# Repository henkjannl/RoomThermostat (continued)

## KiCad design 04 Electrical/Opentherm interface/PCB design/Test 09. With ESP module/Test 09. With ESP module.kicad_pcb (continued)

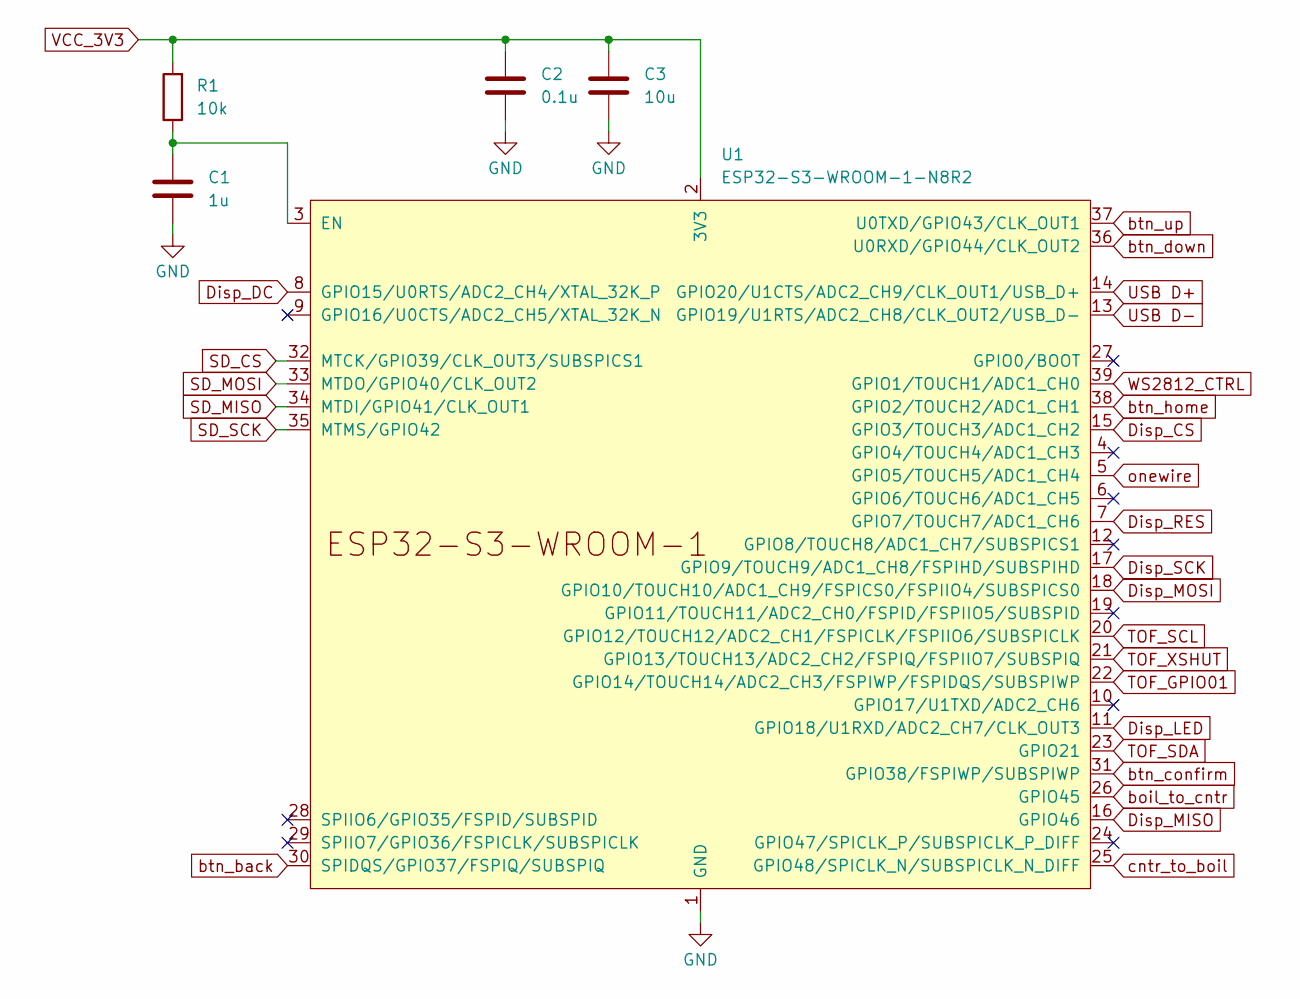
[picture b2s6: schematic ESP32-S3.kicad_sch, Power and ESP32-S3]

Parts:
C1: 1u; C_0603_1608Metric; LCSC Part # C15849
C2: 0.1u; C_0603_1608Metric; LCSC Part # C14663
C3: 10u; C_0402_1005Metric; LCSC Part # C15525
R1: 10k; R_0201_0603Metric; LCSC Part # C25804
U1: ESP32-S3-WROOM-1-N8R2; ESP32-S3-WROOM-1; LCSC Part # C2913204

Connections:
Disp_CS: U1.15 (GPIO3/TOUCH3/ADC1_CH2); also elsewhere on the board
Disp_DC: U1.8 (GPIO15/U0RTS/ADC2_CH4/XTAL_32K_P); also elsewhere on the board
Disp_LED: U1.11 (GPIO18/U1RXD/ADC2_CH7/CLK_OUT3); also elsewhere on the board
Disp_MISO: U1.16 (GPIO46); also elsewhere on the board
Disp_MOSI: U1.18 (GPIO10/TOUCH10/ADC1_CH9/FSPICS0/FSPIIO4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); also elsewhere on the board
Disp_RES: U1.7 (GPIO7/TOUCH7/ADC1_CH6); also elsewhere on the board
Disp_SCK: U1.17 (GPIO9/TOUCH9/ADC1_CH8/FSPIHD/SUBSPIHD); also elsewhere on the board
GND: C1.2, C2.2, C3.2, U1.1 (GND), U1.40 (GND), U1.41 (GND); also elsewhere on the board
unnamed: C1.1, R1.1, U1.3 (EN)
SD_CS: U1.32 (MTCK/GPIO39/CLK_OUT3/SUBSPICS1); also elsewhere on the board
SD_MISO: U1.34 (MTDI/GPIO41/CLK_OUT1); also elsewhere on the board
SD_MOSI: U1.33 (MTDO/GPIO40/CLK_OUT2); also elsewhere on the board
SD_SCK: U1.35 (MTMS/GPIO42); also elsewhere on the board
TOF_GPIO01: U1.22 (GPIO14/TOUCH14/ADC2_CH3/FSPIWP/FSPIDQS/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); also elsewhere on the board
TOF_SCL: U1.20 (GPIO12/TOUCH12/ADC2_CH1/FSPICLK/FSPIIO6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); also elsewhere on the board
TOF_SDA: U1.23 (GPIO21); also elsewhere on the board
TOF_XSHUT: U1.21 (GPIO13/TOUCH13/ADC2_CH2/FSPIQ/FSPIIO7/S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); also elsewhere on the board
USB D+: U1.14 (GPIO20/U1CTS/ADC2_CH9/CLK_OUT1/USB_D+); also elsewhere on the board
USB D-: U1.13 (GPIO19/U1RTS/ADC2_CH8/CLK_OUT2/USB_D-); also elsewhere on the board
VCC_3V3: C2.1, C3.1, R1.2, U1.2 (3V3); also elsewhere on the board
WS2812_CTRL: U1.39 (GPIO1/TOUCH1/ADC1_CH0); also elsewhere on the board
boil_to_cntr: U1.26 (GPIO45); also elsewhere on the board
btn_back: U1.30 (SPIDQS/GPIO37/FSPIQ/SUBSPIQ); also elsewhere on the board
btn_confirm: U1.31 (GPIO38/FSPIWP/SUBSPIWP); also elsewhere on the board
btn_down: U1.36 (U0RXD/GPIO44/CLK_OUT2); also elsewhere on the board
btn_home: U1.38 (GPIO2/TOUCH2/ADC1_CH1); also elsewhere on the board
btn_up: U1.37 (U0TXD/GPIO43/CLK_OUT1); also elsewhere on the board
cntr_to_boil: U1.25 (GPIO48/SPICLK_N/SUBSPICLK_N_DIFF); also elsewhere on the board
onewire: U1.5 (GPIO5/TOUCH5/ADC1_CH4); also elsewhere on the board

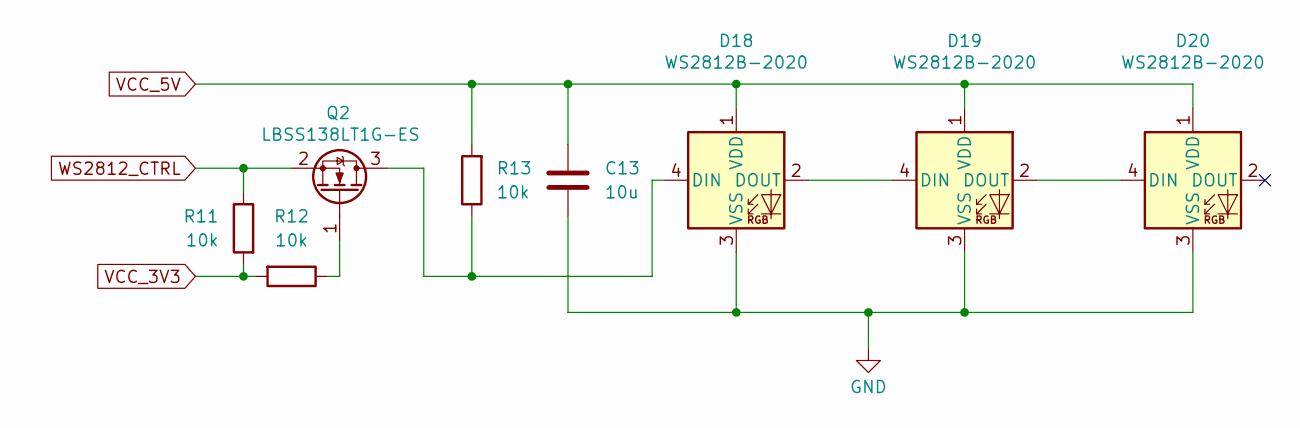
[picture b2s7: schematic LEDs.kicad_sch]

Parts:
C13: 10u; C_0402_1005Metric; LCSC Part # C15525
D18, D19, D20: WS2812B-2020; LED_WS2812B_PLCC4_5.0x5.0mm_P3.2mm; LCSC Part # C965555
Q2: LBSS138LT1G-ES; SOT-23; LCSC Part # C5224262
R11, R12, R13: 10k; R_0201_0603Metric; LCSC Part # C25804

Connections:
GND: C13.2, D18.3 (VSS), D19.3 (VSS), D20.3 (VSS); also elsewhere on the board
unnamed: D18.4 (DIN), Q2.3 (D), R13.1
unnamed: D18.2 (DOUT), D19.4 (DIN)
unnamed: D19.2 (DOUT), D20.4 (DIN)
unnamed: Q2.1 (G), R12.1
VCC_3V3: R11.2, R12.2; also elsewhere on the board
VCC_5V: C13.1, D18.1 (VDD), D19.1 (VDD), D20.1 (VDD), R13.2; also elsewhere on the board
WS2812_CTRL: Q2.2 (S), R11.1; also elsewhere on the board

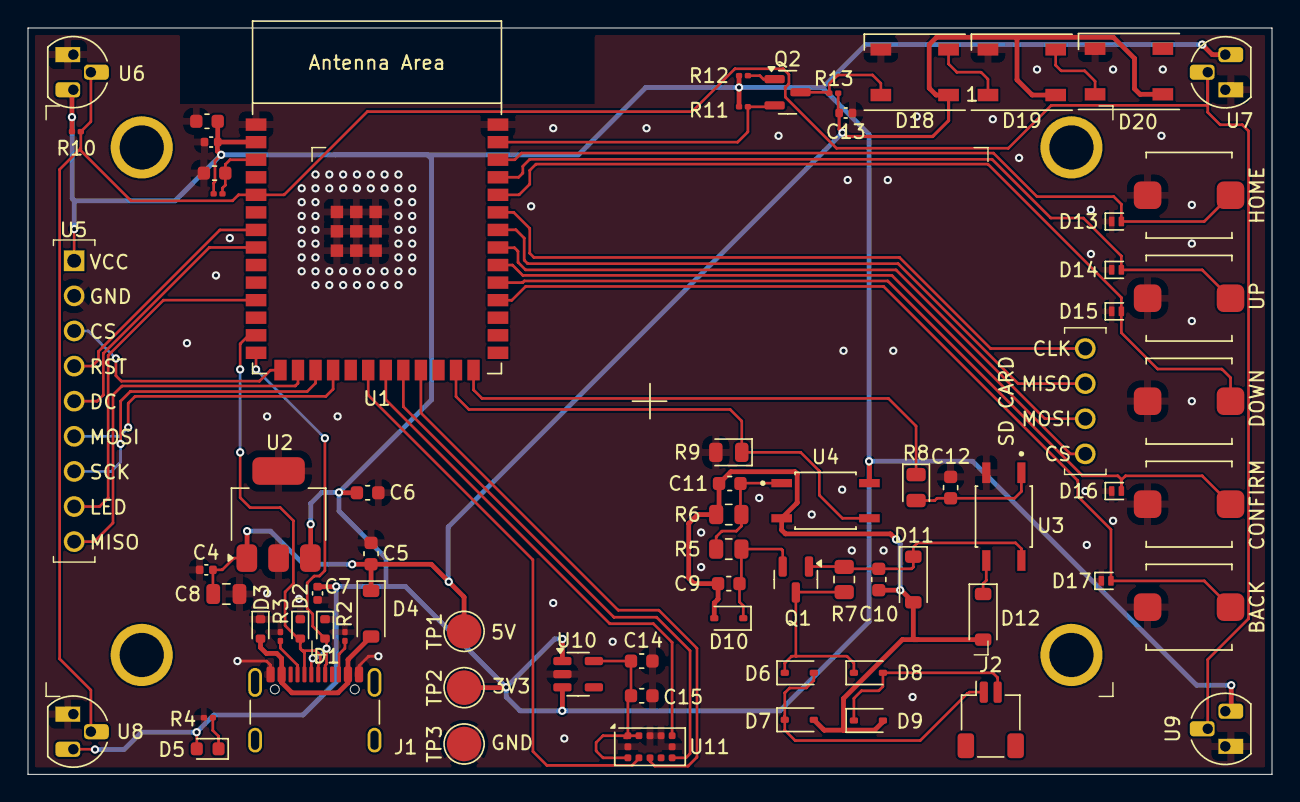
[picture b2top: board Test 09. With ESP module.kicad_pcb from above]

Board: 2 copper layers, 90.0 x 54.0 mm, 71 parts (0 on the bottom side), 48 nets.

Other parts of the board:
D13, D14, D15, D16, D17: LESD8D3.3CAT5G-ES; D_SOD-882
SW1: btn_home; SW_Push_SPEH
SW2: btn_up; SW_Push_SPEH
SW3: btn_down; SW_Push_SPEH
SW4: btn_confirm; SW_Push_SPEH
SW5: btn_back; SW_Push_SPEH

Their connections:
GND: D13.1 (A1), D14.1 (A1), D15.1 (A1), D16.1 (A1), D17.1 (A1), SW1.1, SW2.1, SW3.1, SW4.1, SW5.1; also elsewhere on the board
btn_back: D17.2 (A2), SW5.2; also elsewhere on the board
btn_confirm: D16.2 (A2), SW4.2; also elsewhere on the board
btn_down: D15.2 (A2), SW3.2; also elsewhere on the board
btn_home: D13.2 (A2), SW1.2; also elsewhere on the board
btn_up: D14.2 (A2), SW2.2; also elsewhere on the board

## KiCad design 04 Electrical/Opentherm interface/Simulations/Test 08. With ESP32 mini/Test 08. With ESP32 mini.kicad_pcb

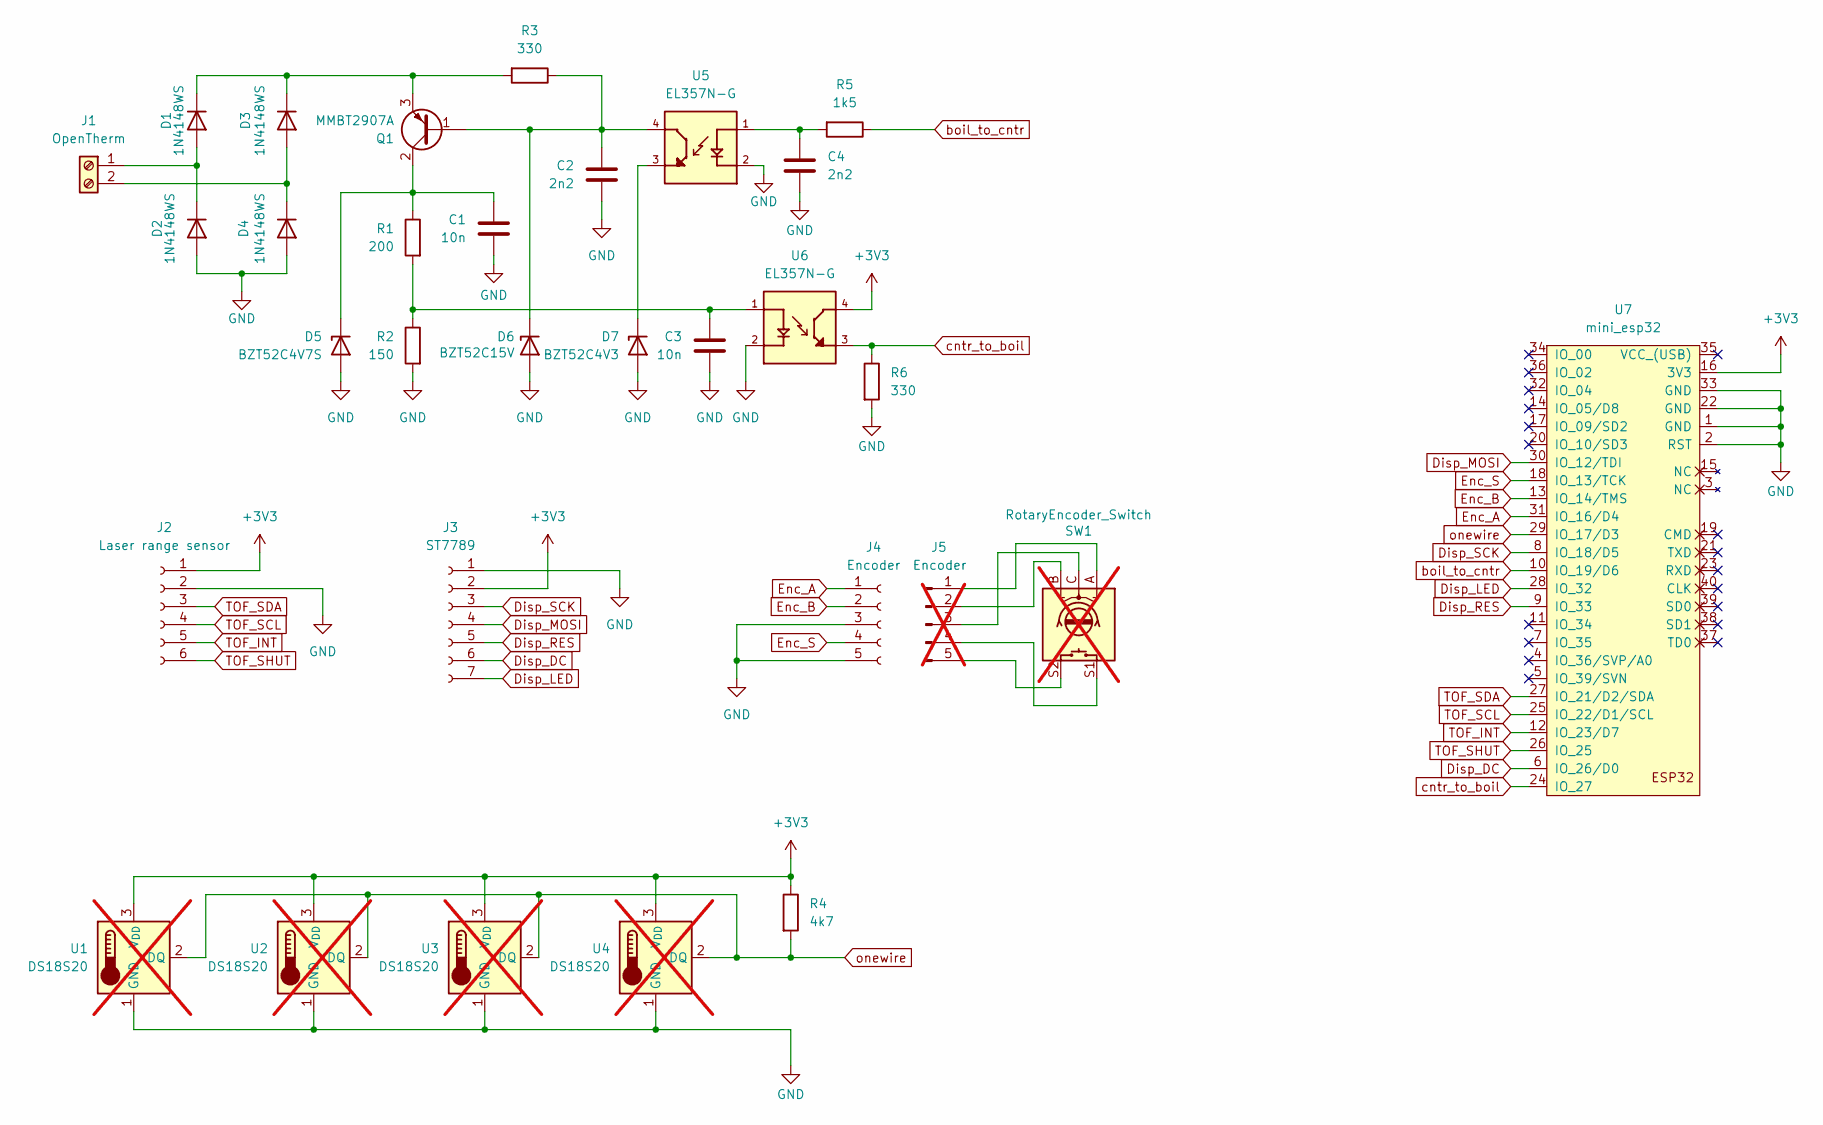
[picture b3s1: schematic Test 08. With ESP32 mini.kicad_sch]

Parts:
C1, C3: 10n; C_0603_1608Metric
C2, C4: 2n2; C_0603_1608Metric
D1, D2, D3, D4: 1N4148WS; D_SOD-323
D5: BZT52C4V7S; D_SOD-323
D6: BZT52C15V; D_SOD-123
D7: BZT52C4V3; D_SOD-123
J1: OpenTherm; TerminalBlock_bornier-2_P5.08mm
J2: Laser range sensor; PinHeader_1x06_P2.54mm_Vertical
J3: ST7789; PinHeader_1x07_P2.54mm_Vertical
J4: Encoder; PinHeader_1x05_P2.54mm_Vertical
J5: Encoder; not fitted
Q1: MMBT2907A; SOT-23
R1: 200; R_0805_2012Metric
R2: 150; R_0805_2012Metric
R3: 330; R_0805_2012Metric
R4: 4k7; R_0805_2012Metric
R5: 1k5; D_0805_2012Metric
R6: 330; D_0805_2012Metric
SW1: RotaryEncoder_Switch; not fitted
U1, U2, U3, U4: DS18S20; TO-92L_HandSolder; not fitted
U5, U6: EL357N-G; OPTO_EL357N-G; PARTREV 6
U7: mini_esp32; ESP32_mini

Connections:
+3V3: J2.1, J3.2, R4.1, U1.3 (V_{DD}), U2.3 (V_{DD}), U3.3 (V_{DD}), U4.3 (V_{DD}), U6.4, U7.16 (3V3)
Disp_DC: J3.6, U7.6 (IO_26/D0)
Disp_LED: J3.7, U7.28 (IO_32)
Disp_MOSI: J3.4, U7.30 (IO_12/TDI)
Disp_RES: J3.5, U7.9 (IO_33)
Disp_SCK: J3.3, U7.8 (IO_18/D5)
Enc_A: J4.1, U7.31 (IO_16/D4)
Enc_B: J4.2, U7.13 (IO_14/TMS)
Enc_S: J4.4, U7.18 (IO_13/TCK)
GND: C1.1, C2.2, C3.1, C4.1, D2.2 (A), D4.2 (A), D5.2 (A), D6.2 (A), D7.2 (A), J2.2, J3.1, J4.3, J4.5, R2.2, R6.2, U1.1 (GND), U2.1 (GND), U3.1 (GND), U4.1 (GND), U5.2, U6.2, U7.1 (GND), U7.2 (RST), U7.22 (GND), U7.33 (GND)
unnamed: C3.2, R1.2, R2.1, U6.1
unnamed: C4.2, R5.2, U5.1
unnamed: D1.2 (A), D2.1 (K), J1.1
unnamed: D1.1 (K), D3.1 (K), Q1.3 (E), R3.2
unnamed: D3.2 (A), D4.1 (K), J1.2
unnamed: C1.2, D5.1 (K), Q1.2 (C), R1.1
unnamed: C2.1, D6.1 (K), Q1.1 (B), R3.1, U5.4
unnamed: D7.1 (K), U5.3
unnamed: J5.1, SW1.A
unnamed: J5.2, SW1.B
unnamed: J5.3, SW1.C
unnamed: J5.4, SW1.S1
unnamed: J5.5, SW1.S2
TOF_INT: J2.5, U7.12 (IO_23/D7)
TOF_SCL: J2.4, U7.25 (IO_22/D1/SCL)
TOF_SDA: J2.3, U7.27 (IO_21/D2/SDA)
TOF_SHUT: J2.6, U7.26 (IO_25)
boil_to_cntr: R5.1, U7.10 (IO_19/D6)
cntr_to_boil: R6.1, U6.3, U7.24 (IO_27)
onewire: R4.2, U1.2 (DQ), U2.2 (DQ), U3.2 (DQ), U4.2 (DQ), U7.29 (IO_17/D3)

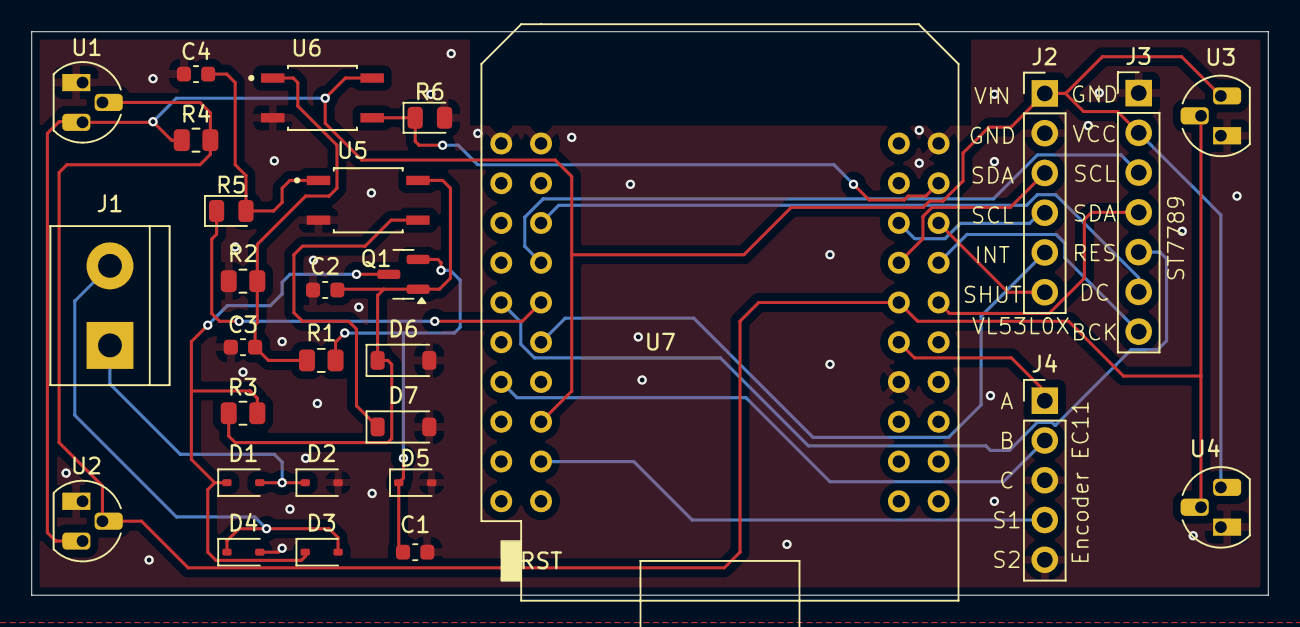
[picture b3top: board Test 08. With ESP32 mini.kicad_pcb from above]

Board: 2 copper layers, 79.0 x 36.0 mm, 29 parts (0 on the bottom side), 25 nets.

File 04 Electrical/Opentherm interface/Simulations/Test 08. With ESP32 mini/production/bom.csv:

Designator,Footprint,Quantity,Value,LCSC Part #
"C1, C3",0603,2,10n,
"C2, C4",0603,2,2n2,
"D1, D2, D3, D4",D_SOD-323,4,1N4148WS,
D5,D_SOD-323,1,BZT52C4V7S,
D6,D_SOD-123,1,BZT52C15V,
D7,D_SOD-123,1,BZT52C4V3,
Q1,SOT-23,1,MMBT2907A,
R1,0805,1,200,
R2,0805,1,150,
"R3, R6",0805,2,330,
R4,0805,1,4k7,
R5,0805,1,1k5,
"U5, U6",OPTO_EL357N-G,2,EL357N-G,

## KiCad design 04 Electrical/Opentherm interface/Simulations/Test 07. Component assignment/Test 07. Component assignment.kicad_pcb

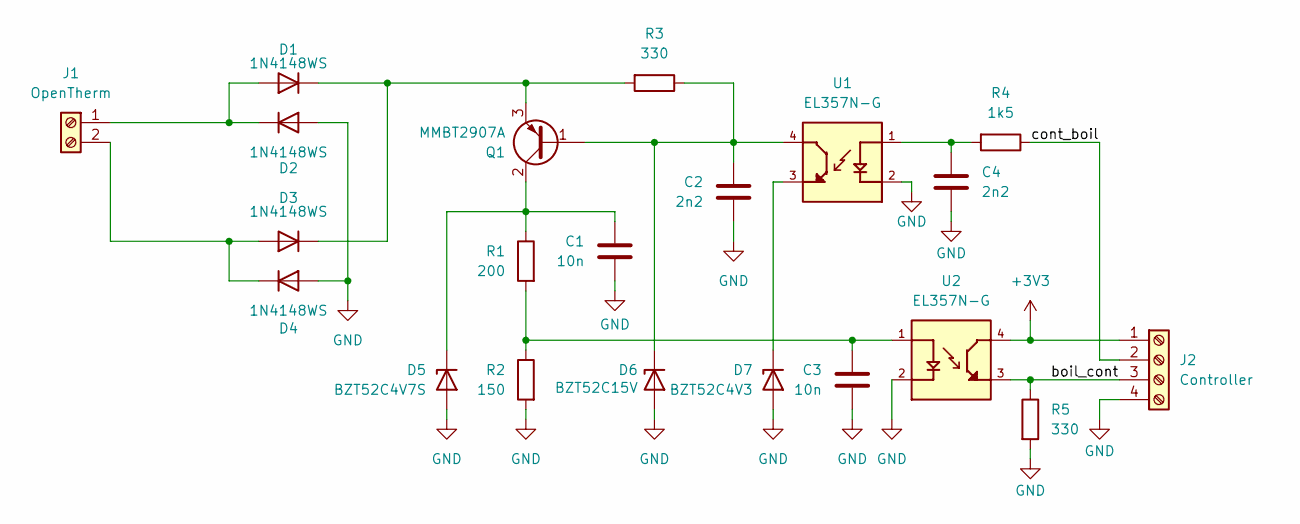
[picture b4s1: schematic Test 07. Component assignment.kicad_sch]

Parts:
C1, C3: 10n; C_0603_1608Metric
C2, C4: 2n2; C_0603_1608Metric
D1, D2, D3, D4: 1N4148WS; D_SOD-323
D5: BZT52C4V7S; D_SOD-323
D6: BZT52C15V; D_SOD-123
D7: BZT52C4V3; D_SOD-123
J1: OpenTherm; TerminalBlock_bornier-2_P5.08mm
J2: Controller; TerminalBlock_bornier-4_P5.08mm
Q1: MMBT2907A; SOT-23
R1: 200; R_0805_2012Metric
R2: 150; R_0805_2012Metric
R3: 330; R_0805_2012Metric
R4: 1k5; R_0805_2012Metric
R5: 330; D_0805_2012Metric
U1, U2: EL357N-G; OPTO_EL357N-G; PARTREV 6

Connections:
+3V3: J2.1, U2.4
/boil_cont: J2.3, R5.1, U2.3
/cont_boil: J2.2, R4.1
GND: C1.1, C2.2, C3.1, C4.1, D2.2 (A), D4.2 (A), D5.2 (A), D6.2 (A), D7.2 (A), J2.4, R2.2, R5.2, U1.2, U2.2
unnamed: C3.2, R1.2, R2.1, U2.1
unnamed: C4.2, R4.2, U1.1
unnamed: D1.2 (A), D2.1 (K), J1.1
unnamed: D1.1 (K), D3.1 (K), Q1.3 (E), R3.2
unnamed: D3.2 (A), D4.1 (K), J1.2
unnamed: C1.2, D5.1 (K), Q1.2 (C), R1.1
unnamed: C2.1, D6.1 (K), Q1.1 (B), R3.1, U1.4
unnamed: D7.1 (K), U1.3

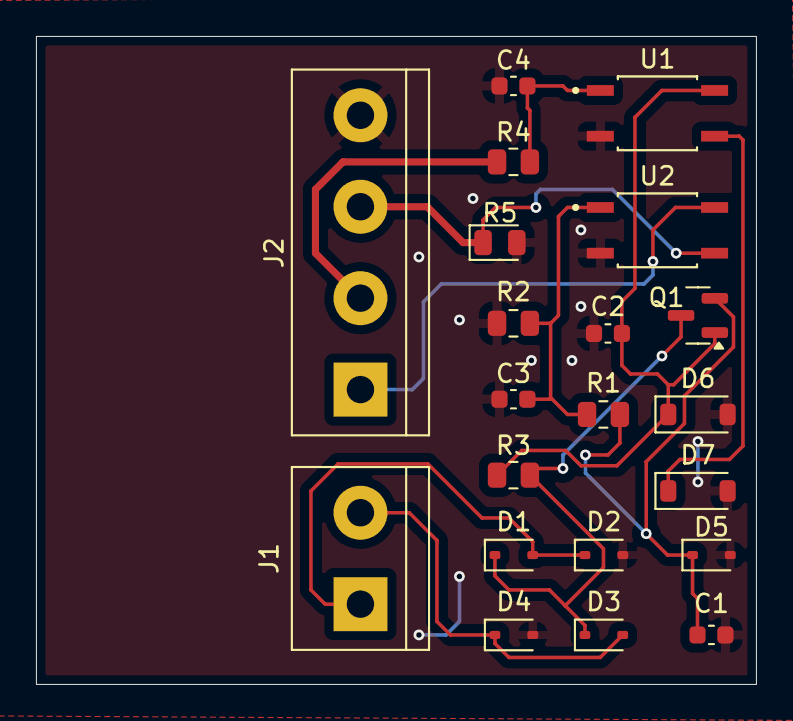
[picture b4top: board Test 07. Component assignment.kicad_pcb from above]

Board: 2 copper layers, 40.0 x 36.0 mm, 21 parts (0 on the bottom side), 12 nets.

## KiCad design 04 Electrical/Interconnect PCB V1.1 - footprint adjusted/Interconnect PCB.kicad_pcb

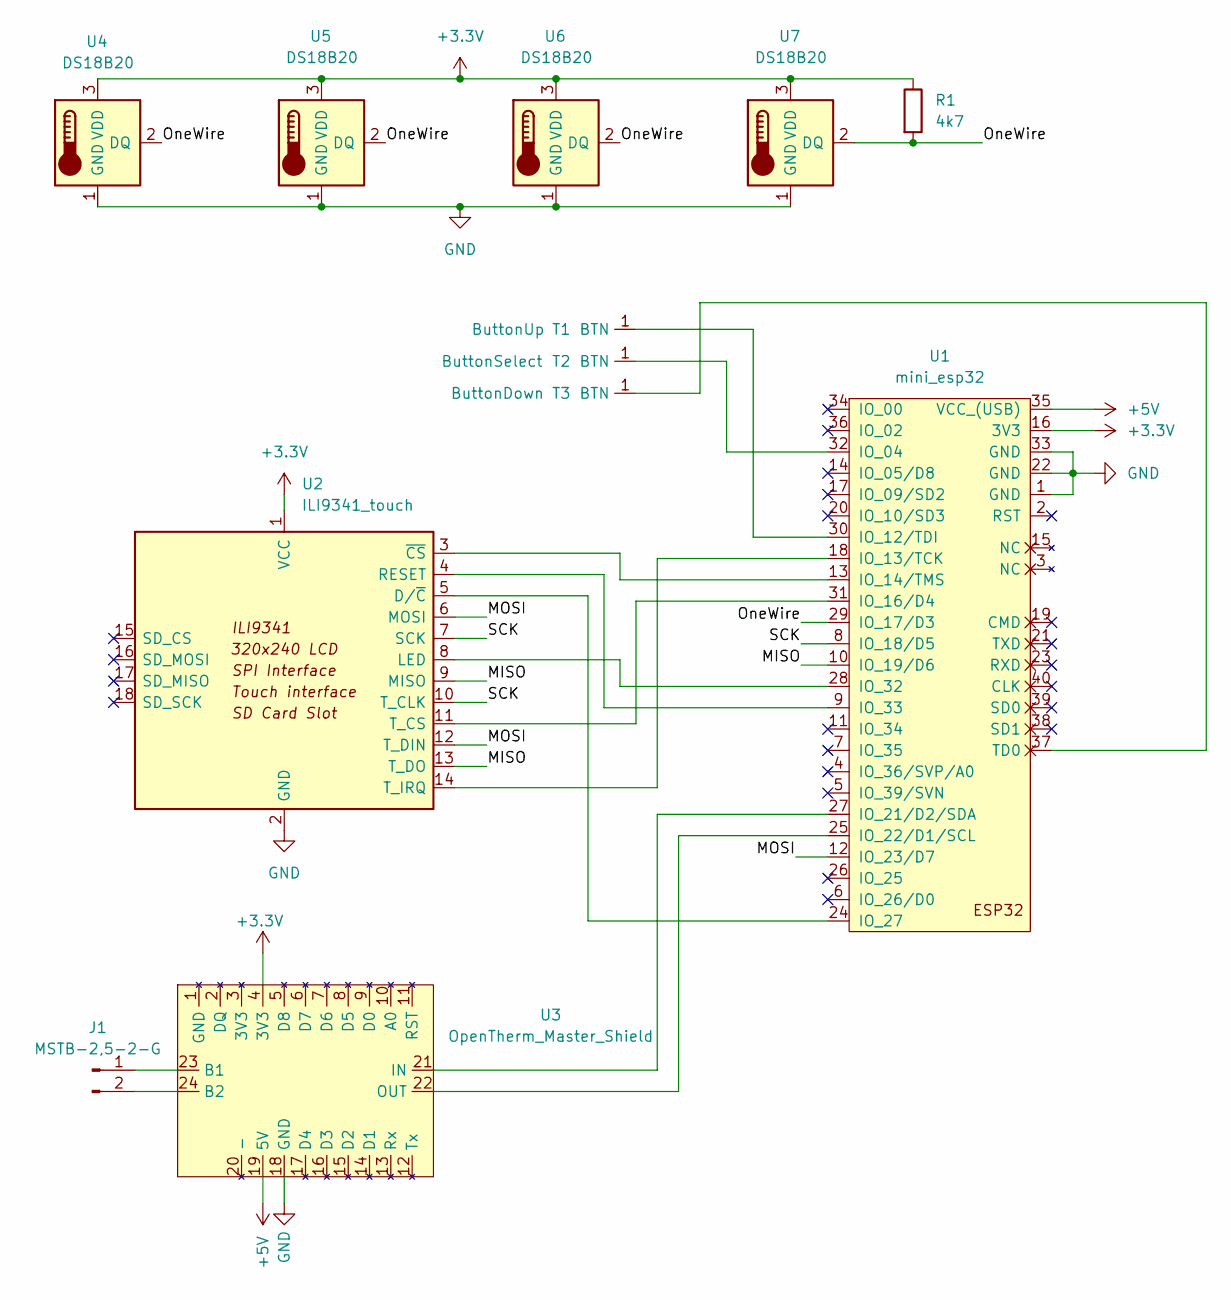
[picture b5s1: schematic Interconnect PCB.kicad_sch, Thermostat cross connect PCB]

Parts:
J1: MSTB-2,5-2-G; Phoenix_MSTB-2,5-2-G
R1: 4k7; Resistor
T1: ButtonUp; TouchPin
T2: ButtonSelect; TouchPin
T3: ButtonDown; TouchPin
U1: mini_esp32; ESP32_mini
U2: ILI9341_touch; ILI9341
U3: OpenTherm_Master_Shield; Opentherm Master Shield
U4, U5, U6, U7: DS18B20

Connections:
+3V3: R1.1, U1.16 (3V3), U2.1 (VCC), U3.4 (3V3), U4.3 (VDD), U5.3 (VDD), U6.3 (VDD), U7.3 (VDD)
+5V: U1.35 (VCC_(USB)), U3.19 (5V)
/MISO: U1.10 (IO_19/D6), U2.9 (MISO), U2.13 (T_DO)
/MOSI: U1.12 (IO_23/D7), U2.6 (MOSI), U2.12 (T_DIN)
/OneWire: R1.2, U1.29 (IO_17/D3), U4.2 (DQ), U5.2 (DQ), U6.2 (DQ), U7.2 (DQ)
/SCK: U1.8 (IO_18/D5), U2.7 (SCK), U2.10 (T_CLK)
GND: U1.1 (GND), U1.22 (GND), U1.33 (GND), U2.2 (GND), U3.18 (GND), U4.1 (GND), U5.1 (GND), U6.1 (GND), U7.1 (GND)
unnamed: J1.1, U3.23 (B1)
unnamed: J1.2, U3.24 (B2)
unnamed: T1.1 (BTN), U1.30 (IO_12/TDI)
unnamed: T2.1 (BTN), U1.32 (IO_04)
unnamed: T3.1 (BTN), U1.37 (TD0)
unnamed: U1.9 (IO_33), U2.4 (RESET)
unnamed: U1.13 (IO_14/TMS), U2.3 (~CS)
unnamed: U1.18 (IO_13/TCK), U2.14 (T_IRQ)
unnamed: U1.24 (IO_27), U2.5 (D/~C)
unnamed: U1.25 (IO_22/D1/SCL), U3.22 (OUT)
unnamed: U1.27 (IO_21/D2/SDA), U3.21 (IN)
unnamed: U1.28 (IO_32), U2.8 (LED)
unnamed: U1.31 (IO_16/D4), U2.11 (T_CS)

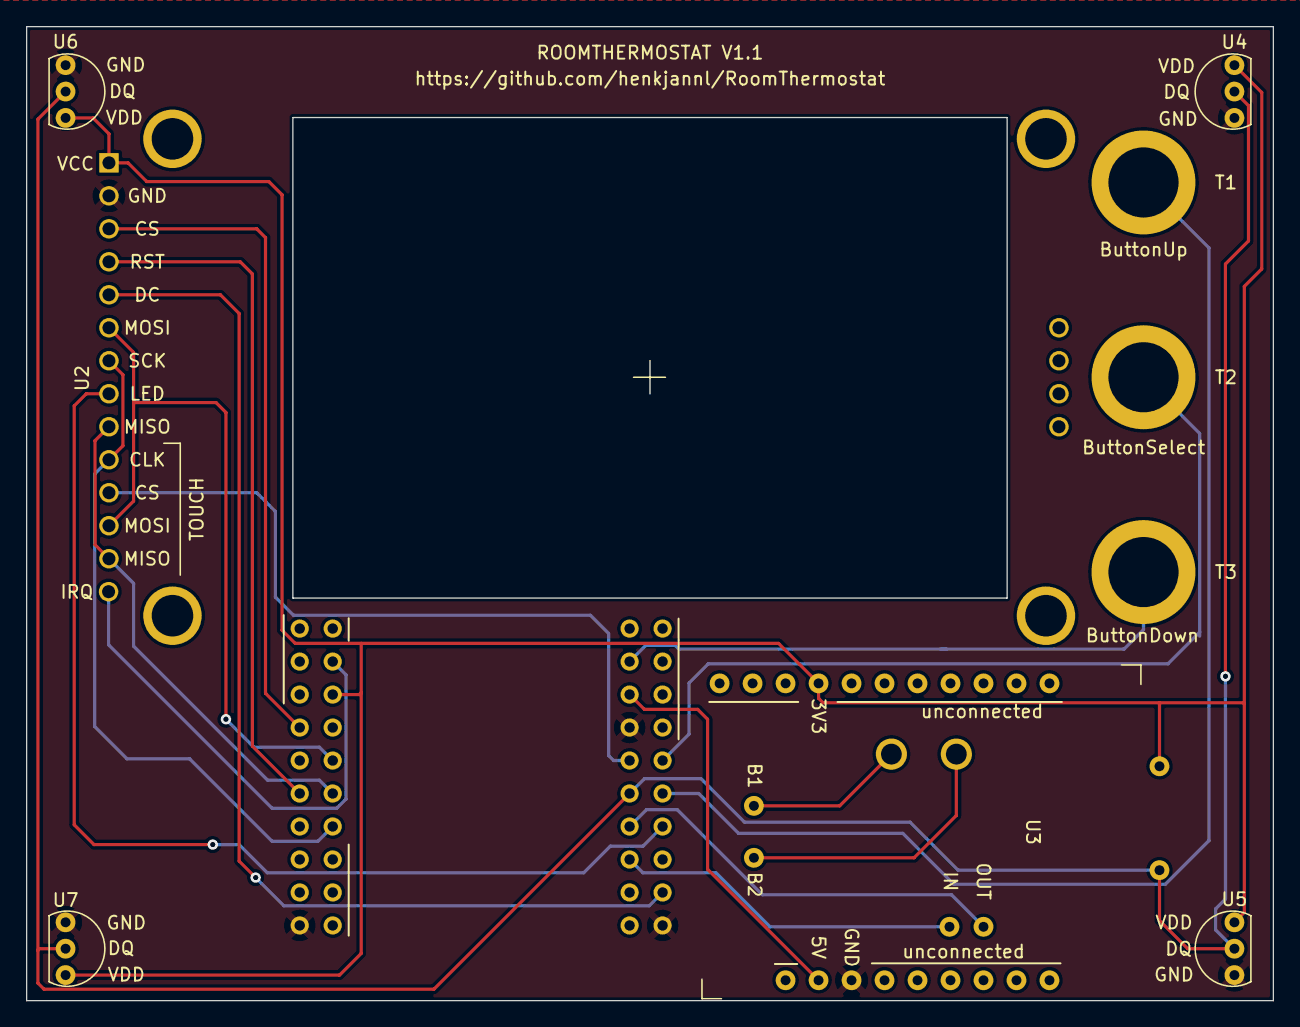
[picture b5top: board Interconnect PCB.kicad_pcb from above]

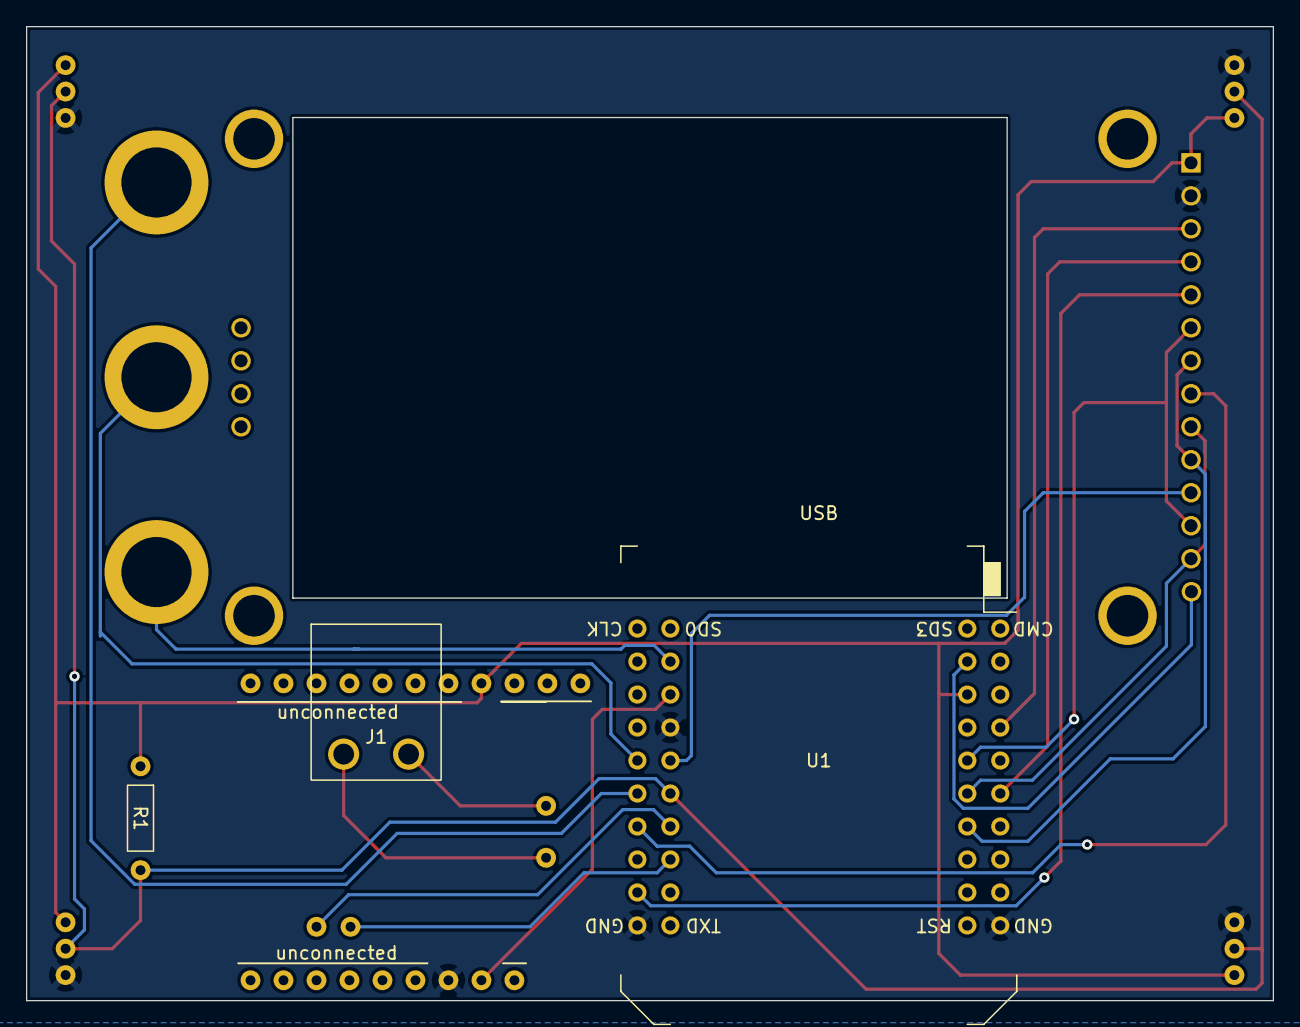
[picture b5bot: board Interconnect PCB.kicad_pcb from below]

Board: 2 copper layers, 96.0 x 75.0 mm, 12 parts (3 on the bottom side), 20 nets.

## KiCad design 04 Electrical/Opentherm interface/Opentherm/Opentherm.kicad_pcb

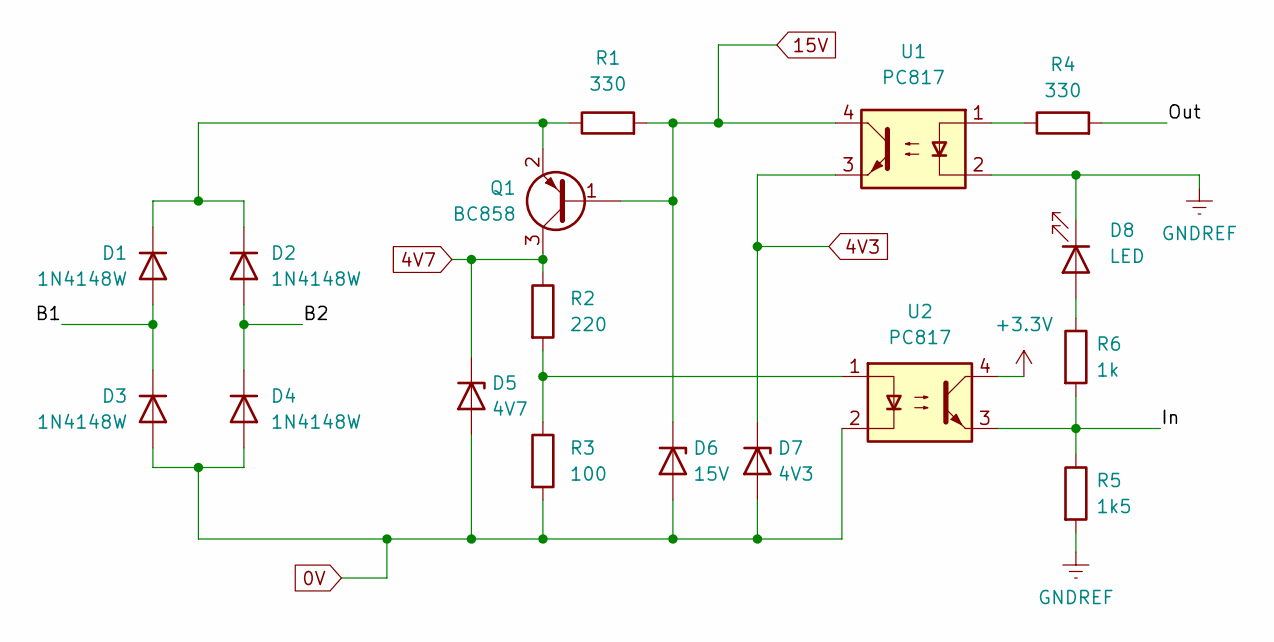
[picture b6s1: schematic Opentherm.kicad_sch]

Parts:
D1, D2, D3, D4: 1N4148W; D_SOD-123
D5: 4V7; D_SOD-123
D6: 15V; D_SOD-123
D7: 4V3; D_SOD-123
D8: LED; D_SOD-123
Q1: BC858; SOT-23
R1, R4: 330; R_1206_3216Metric
R2: 220; R_1206_3216Metric
R3: 100; R_1206_3216Metric
R5: 1k5; R_1206_3216Metric
R6: 1k; R_1206_3216Metric
U1, U2: PC817; SOP-4_3.8x4.1mm_P2.54mm

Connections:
0V: D3.2 (A), D4.2 (A), D5.2 (A), D6.2 (A), D7.2 (A), R3.2, U2.2
4V3: D7.1 (K), U1.3
4V7: D5.1 (K), Q1.3 (C), R2.1
15V: D6.1 (K), Q1.1 (B), R1.2, U1.4
+3V3: U2.4
/B1: D1.2 (A), D3.1 (K)
/B2: D2.2 (A), D4.1 (K)
/In: R5.1, R6.2, U2.3
/Out: R4.2
GNDREF: D8.1 (K), R5.2, U1.2
unnamed: D1.1 (K), D2.1 (K), Q1.2 (E), R1.1
unnamed: D8.2 (A), R6.1
unnamed: R2.2, R3.1, U2.1
unnamed: R4.1, U1.1

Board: 2 copper layers, 17 parts (0 on the bottom side), 12 nets, no tracks yet.

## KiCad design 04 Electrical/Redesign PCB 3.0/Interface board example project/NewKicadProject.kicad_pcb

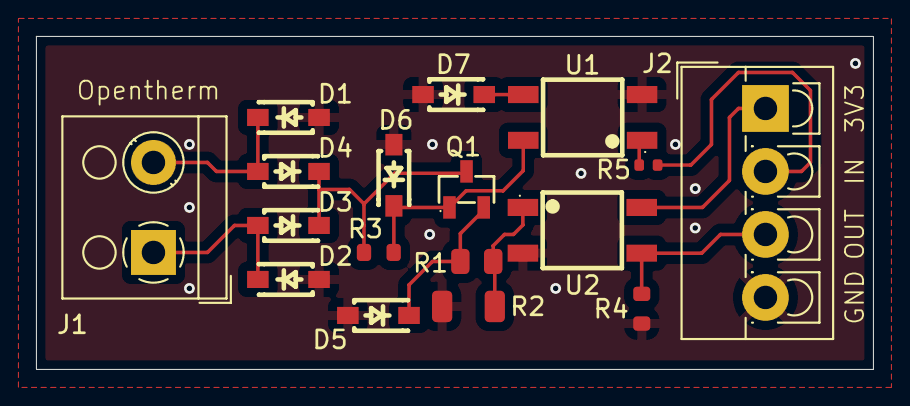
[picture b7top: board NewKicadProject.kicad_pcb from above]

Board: 2 copper layers, 46.5 x 18.5 mm, 17 parts (0 on the bottom side), 12 nets.

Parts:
D1, D2, D3, D4: 1N4448W; SOD-123_L2.7-W1.6-LS3.7-RD-1
D5: 4V7; SOD-123_L2.7-W1.6-LS3.7-RD-1
D6: 15V; SOD-123_L2.7-W1.6-LS3.7-RD-1
D7: 4V3; SOD-123_L2.7-W1.6-LS3.7-RD-1
J1: Boiler; TerminalBlock_RND_205-00001_1x02_P5.00mm_Horizontal
J2: Screw_Terminal_01x04; TerminalBlock_4Ucon_1x04_P3.50mm_Vertical
Q1: BC858; SOT-23-3_L2.9-W1.3-P1.90-LS2.4-BR
R1: 0805,220; 0805_2012Metric
R2: 1206,100; 1206_3216Metric
R3, R4: 0603,330; 0603_1608Metric
R5: 0402,1.5k; 0402_1005Metric
U1, U2: EL357N(C)(TA)-G; OPTO-SMD-4_L4.4-W4.1-P2.54-LS7.0-TL

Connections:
3V3: J2.1, U2.4 (COL)
GND: D1.2 (A), D2.2 (A), D5.2 (A), D6.2 (A), D7.2 (A), J2.4, R2.2, R4.1, U1.2 (CAT), U2.2 (CAT)
IN: J2.2, R5.2
unnamed: D1.1 (K), D4.2 (A), J1.2
unnamed: D2.1 (K), D3.2 (A), J1.1
unnamed: D3.1 (K), D4.1 (K), Q1.3 (E), R3.1
unnamed: D5.1 (K), Q1.2 (C), R1.1
unnamed: D6.1 (K), Q1.1 (B), R3.2, U1.4 (COL)
unnamed: D7.1 (K), U1.3 (EM)
unnamed: R5.1, U1.1 (AN)
unnamed: R1.2, R2.1, U2.1 (AN)
OUT: J2.3, R4.2, U2.3 (EM)

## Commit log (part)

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2022-12-05 Rename template.json
2022-12-05 Adding DeviceReset option
2022-12-06 Temperature update
2022-12-06 Telegram menu clipped
2022-12-07 minor changes
2022-12-08 Holiday example added to readme
2022-12-11 Bugfixes 1.0.6
2022-12-12 Minor tweaks device startup
2022-12-12 Telegram optimizations
2022-12-13 Big update
2022-12-13 Release of V1.0.6
2022-12-13 Clock removed from image
2022-12-14 Tried to resolve issue boiler communiation
2022-12-15 Mechanical design for TTGO
2022-12-20 PCB modifications
2022-12-21 Adjusted polling frequency, the last bug before release
2022-12-21 Release of v1.0.7, first fully working version
2022-12-21 Release of v1.0.7 - first fully working version
2022-12-22 Hide current week schedule for main screen
2022-12-22 Readme update
2022-12-24 Added permanent storage of controller settings
2022-12-25 Over the air software updates added
2022-12-25 OTA updates fixed
2022-12-25 Improved Multiple day response
2022-12-25 V1.1.0 release
2022-12-28 Temporary housing added
2022-12-29 v1.1.1
2022-12-29 Deta example working
2022-12-29 Setpoint priorities added to Readme
2023-01-03 GUI redesign
2023-01-03 Same icons in user interface like in Telegram
2023-01-04 Readme
2023-01-06 Cleaned up print
2023-01-10 Early mechanical concept with rotary encoder added
2023-01-12 Weekend icon changed, startup command implemented
2023-01-13 Wall thickness for magnets increased
2023-01-23 Emoticons for daytypes more generic
2023-01-23 Emoticons
2023-01-26 Introduction to AsyncTelegram2
2023-02-01 Test with CSV logfile added
2023-02-02 Dynamic keyboard working with ASyncTelegram
2023-05-29 Various changes
2023-12-10 Opentherm documentation
2024-09-17 Squareline Studio
2024-09-19 Opentherm interface example project
2024-09-24 Reverse engineering OpenTherm
2024-09-26 Test circuits KiCad simulation
2024-09-28 PCB design (without ESP32) completed
2024-09-28 ESP32 integrated
2024-10-06 Electrical interface
2024-10-07 Added schematic sheet
2024-10-15 First version of PCB without errors
2024-10-15 Schematic update
2024-10-15 SPI port on default pins
2024-10-25 Component assignment
2024-11-16 Redesign PCB
2024-11-18 Routing PCB test 9
2024-11-25 Logo added to PCB
2024-11-27 As ordered at JLCPCB
2024-11-27 As ordered V3.0 at JLCPCB
2024-12-04 Housing
2025-01-17 Photo of PCB added
2025-11-01 v2.0 for PlatformIO
